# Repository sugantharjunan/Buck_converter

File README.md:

# DC-DC Buck Converter – KiCad PCB Design

A compact and efficient **DC-DC Buck Converter** designed using **KiCad EDA** for schematic capture and PCB layout. This project converts higher DC input voltage into a stable lower DC output with improved efficiency compared to linear regulators.

The design includes voltage regulation, filtering, feedback control, and status indication circuits suitable for embedded systems, IoT applications, battery-powered devices, and electronics prototyping.

---

## Project Overview

This project demonstrates the design and implementation of a **Buck Converter PCB** using:

* Schematic Design in KiCad
* PCB Layout Design
* 3D PCB Visualization
* Power Regulation Circuit
* Adjustable Output Voltage

The converter is designed for efficient DC voltage step-down applications.

---

# Features

* Adjustable DC output voltage
* Compact PCB layout
* High-efficiency switching regulation
* LED power indication
* Feedback-based voltage control
* 3D PCB design included
* Designed using KiCad

---

# Software Used

* KiCad

Official Website: [KiCad Official Website](https://www.kicad.org?utm_source=chatgpt.com)

---

# Hardware Components

| Component      | Description               |
| -------------- | ------------------------- |
| XL4015         | DC-DC Buck Converter IC   |
| 78L05          | 5V Voltage Regulator      |
| LM358          | Operational Amplifier     |
| Schottky Diode | Fast switching diode      |
| Inductor       | Energy storage component  |
| Capacitors     | Input/Output filtering    |
| Potentiometer  | Output voltage adjustment |
| LEDs           | Status indicators         |

---

# Project Structure

```bash id="53r1kx"
BUCK-CONVERTER/
│
├── Schematic/
│   └── buck_converter.kicad_sch
│
├── PCB/
│   └── buck_converter.kicad_pcb
│
├── Gerber/
│   └── Manufacturing_Files
│
├── Images/
│   ├── BUCK_CONVERTER_3D.png
│   ├── BUCK_CONVERTER_PCB.png
│   └── BUCK_CONVERTER_SCHEMATIC.png
│
└── README.md
```

---

# Circuit Description

The circuit is based on the **XL4015 buck converter IC**, which performs efficient voltage step-down conversion.

## Working Principle

1. DC input voltage is supplied to the converter.
2. XL4015 switches the input at high frequency.
3. Inductor and capacitor filter the switching waveform.
4. Schottky diode improves efficiency and protects the circuit.
5. Feedback network regulates the output voltage.
6. LM358 comparator section provides monitoring and indication.

---

# PCB Design

The PCB was designed with:

* Optimized power trace routing
* Compact component placement
* Proper grounding
* Heat management considerations
* Easy soldering access
* Single-board integrated design

---

# Electrical Specifications

| Parameter         | Value                |
| ----------------- | -------------------- |
| Converter Type    | DC-DC Buck Converter |
| Main IC           | XL4015               |
| Input Voltage     | 8V – 36V DC          |
| Adjustable Output | Yes                  |
| PCB Tool          | KiCad                |
| Regulation Type   | Switching            |

---

# Applications

* Embedded Systems
* IoT Devices
* Battery Charging Systems
* Robotics
* Portable Electronics
* Microcontroller Power Supply
* DIY Electronics Projects

---

# Output Voltage Adjustment

The output voltage can be adjusted using the onboard potentiometer:

* Rotate clockwise → Increase voltage
* Rotate counterclockwise → Decrease voltage

Do not exceed component voltage ratings.

---

# Future Improvements

* Add current limiting protection
* Add thermal shutdown circuit
* Add digital voltage display
* Improve EMI filtering
* Add USB-C power output

This project is open-source and available under the MIT License.

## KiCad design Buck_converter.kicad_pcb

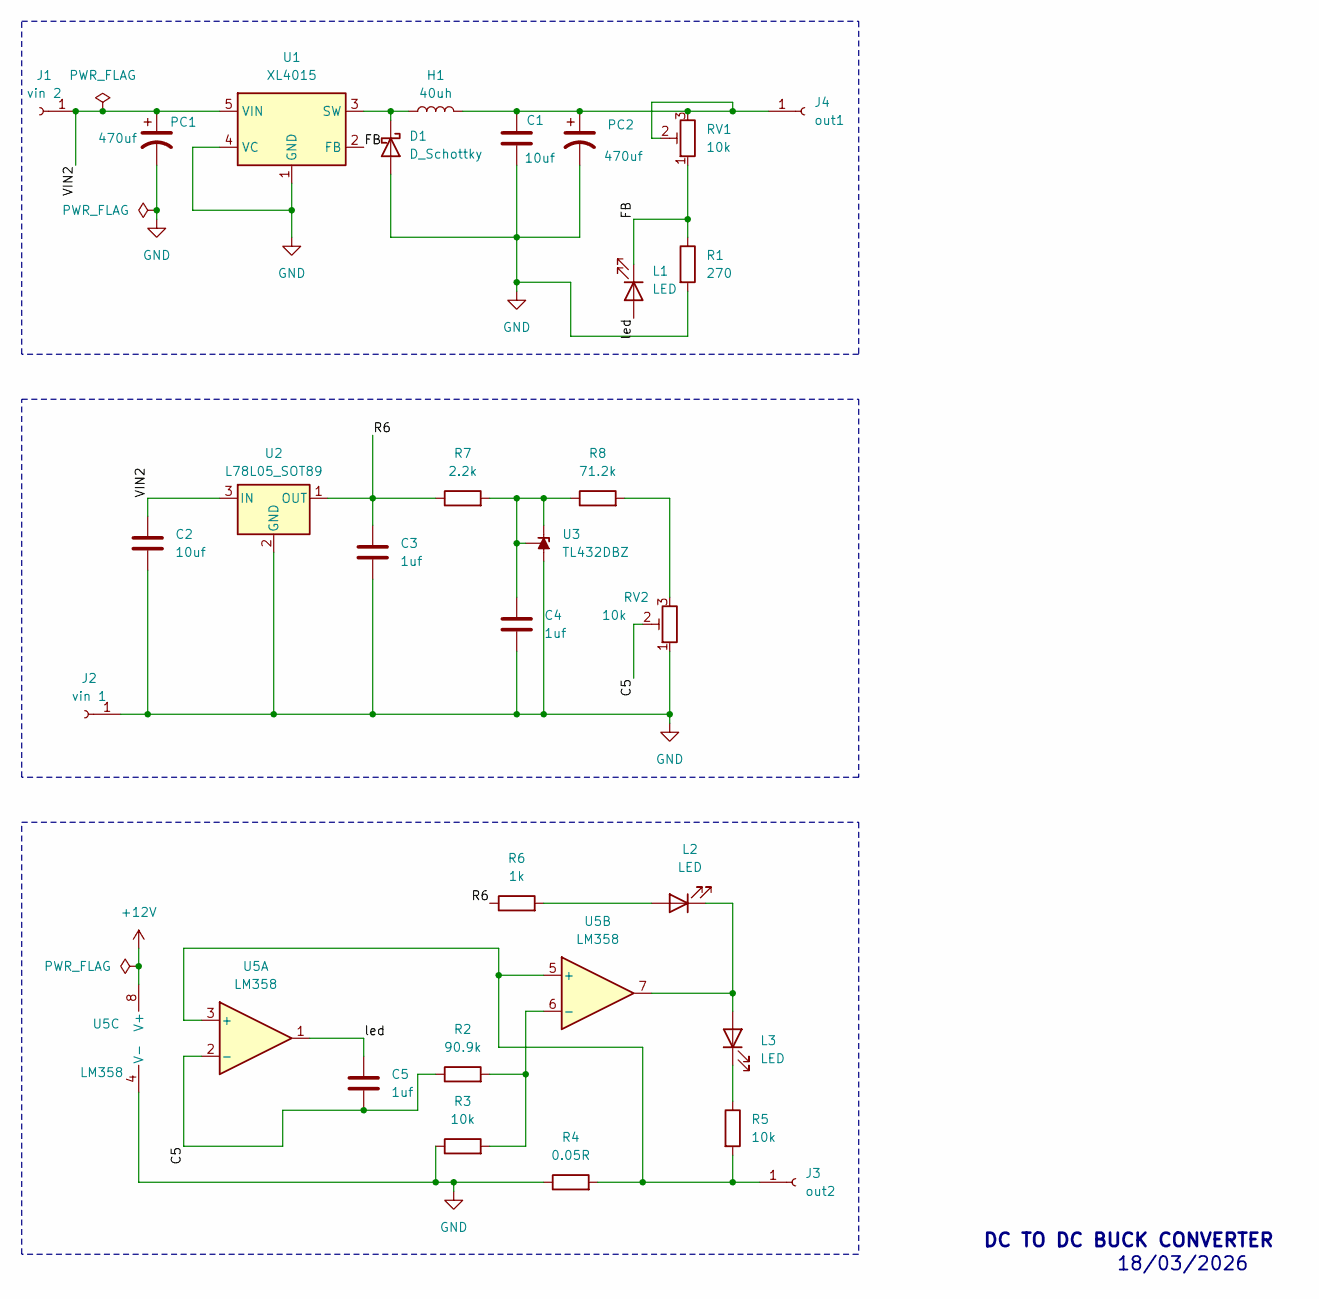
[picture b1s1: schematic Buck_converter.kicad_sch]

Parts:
C1, C2: 10uf; C_1206_3216Metric
C3, C4, C5: 1uf; C_0805_2012Metric
D1: D_Schottky; D_SMA
H1: 40uh; L_Toroid_Vertical_L16.3mm_W7.1mm_P7.11mm_Pulse_H
J1: vin 2; PinSocket_1x01_P2.00mm_Vertical
J2: vin 1; PinSocket_1x01_P2.00mm_Vertical
J3: out2; PinSocket_1x01_P2.00mm_Vertical
J4: out1; PinSocket_1x01_P2.00mm_Vertical
L1, L2, L3: LED; LED_0402_1005Metric
PC1, PC2: 470uf; CP_Elec_6.3x5.4
R1: 270; R_0805_2012Metric
R2: 90.9k; R_0805_2012Metric
R3, R5: 10k; R_0805_2012Metric
R4: 0.05R; R_2512_6332Metric
R6: 1k; R_0805_2012Metric
R7: 2.2k; R_0805_2012Metric
R8: 71.2k; R_0805_2012Metric
RV1, RV2: 10k; Potentiometer_Bourns_3296W_Vertical
U1: XL4015; TO-263-5_TabPin3
U2: L78L05_SOT89; SOT-89-3
U3: TL432DBZ; SOT-23
U5: LM358; SOIC-8_3.9x4.9mm_P1.27mm

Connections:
+12V: U5.8 (V+)
/C5: C5.2, R2.1, RV2.2, U5.2 (-)
/FB: L1.1 (K), R1.1, RV1.1, U1.2 (FB)
/R6: C3.1, R6.1, R7.1, U2.1 (OUT)
/VIN2: C2.1, J1.1, PC1.1, U1.5 (VIN), U2.3 (IN)
/led: C5.1, L1.2 (A), U5.1
GND: C1.2, C2.2, C3.2, C4.2, D1.2 (A), J2.1, PC1.2, PC2.2, R1.2, R3.1, R4.1, RV2.1, U1.1 (GND), U1.4 (VC), U2.2 (GND), U3.3 (A), U5.4 (V-)
unnamed: D1.1 (K), H1.1, U1.3 (SW)
unnamed: J3.1, R4.2, R5.2, U5.3 (+), U5.5 (+)
unnamed: C1.1, H1.2, J4.1, PC2.1, RV1.2, RV1.3
unnamed: L2.2 (A), R6.2
unnamed: L2.1 (K), L3.2 (A), U5.7
unnamed: L3.1 (K), R5.1
unnamed: R8.2, RV2.3
unnamed: C4.1, R7.2, R8.1, U3.1 (REF), U3.2 (K)
unnamed: R2.2, R3.2, U5.6 (-)

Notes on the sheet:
18/03/2026
DC TO DC BUCK CONVERTER

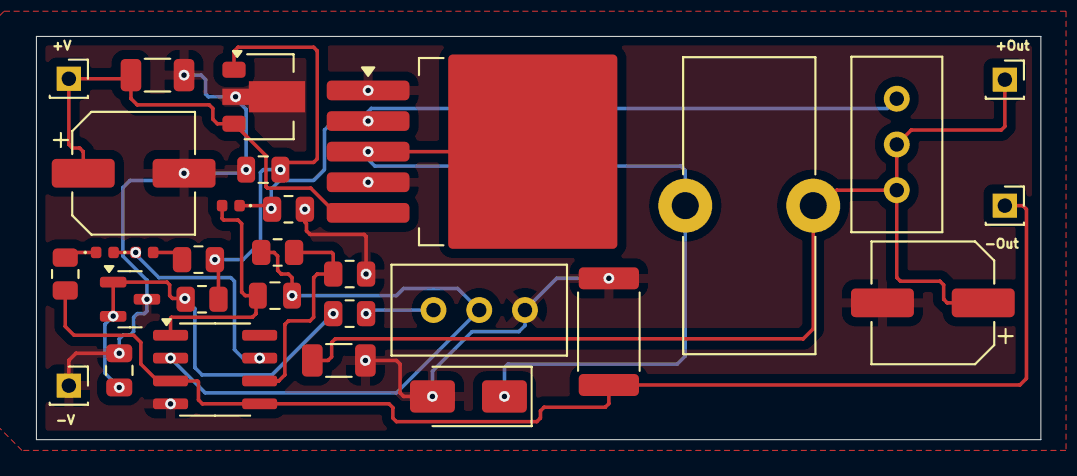
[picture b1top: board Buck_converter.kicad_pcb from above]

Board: 2 copper layers, 55.8 x 22.4 mm, 30 parts (0 on the bottom side), 15 nets.

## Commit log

2026-03-21 File upload
2026-03-24 Buck_converter_Schmetic
2026-03-24 Buck_converter_3D
2026-03-24 Buck_converter_3D 1
